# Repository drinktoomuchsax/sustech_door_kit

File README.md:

<div>
<p align="center">

  </p>  
<h1 align="center">
  南科大宿舍门锁套件
</h1>
<p align="center">
  丢掉你的校园卡
</p>
<p align="center">
人脸识别、模糊密码、电子反锁、访客密码、无痕恢复……</a>
</p>
</div>

_This page is not available in [English](README.en.md) yet._ 

:unlock:这个项目使用两片ESP32开发板以及一系列模块，将宿舍开门体验提到了新高度

:star:欢迎Star

:+1:项目采用CC0协议，欢迎复刻、商用、传播

:poop:假如你想在此基础上开发新功能，看不懂屎山代码或有任何疑惑，欢迎issue

---

# :world_map:Table of Contents
- [功能](#功能)
- [原理](#原理)
- [复刻](#复刻)
  - [:money\_with\_wings:物料清单（全功能-预算敏感版本）](#money_with_wings物料清单全功能-预算敏感版本)
  - [:wrench:所需工具](#wrench所需工具)
  - [门的部分](#门的部分)
  - [门内模块（inModule）](#门内模块inmodule)
  - [门外模块（exModule）](#门外模块exmodule)
- [To Do](#to-do)

# 功能

# 原理
拆开门发现有调试的线，详见[博客](wait-to-be-writed)

# 复刻
本项目在开始之初的设计目标之一就是尽可能低的复刻门槛，所以使用的都是现成的市售模块。虽然牺牲了一些集成度和成本，但是你不需要经历繁复地采购和焊接贴片元件，只需少许简单焊接和组装就能复刻本项目。

如果对某一步的详细程度感到不满意或有任何疑惑，欢迎提交issue。

如果你的网络有问题不能加载出图片，可以看南科手册上的版本。

## :money_with_wings:物料清单（全功能-预算敏感版本）
> 第一步，下面全部买回来

| n       | 名称                      | 数量 | 款式                                             | 总价         | 链接                                                                                                                                         | 备注                                                                                                                                                             |
| ------- | ------------------------- | ---- | ------------------------------------------------ | ------------ | -------------------------------------------------------------------------------------------------------------------------------------------- | ---------------------------------------------------------------------------------------------------------------------------------------------------------------- |
| 0       | luat esp32-s3开发板       | 1片  | ESP32S3开发板                                    | ￥29.9        | [淘宝合宙旗舰店](https://item.taobao.com/item.htm?spm=a1z09.2.0.0.67002e8dnQlfYj&id=696836421009&_u=53t2jj8gb611)                            | 可以换其他家，但是记得修改pcb封装尺寸和代码引脚定义                                                                                                              |
| 1       | luat esp32-c3开发板       | 1片  | 经典款ESP32C3开发板                              | ￥12.9        | [淘宝合宙旗舰店](https://item.taobao.com/item.htm?spm=a1z09.2.0.0.67002e8dnQlfYj&id=666579064570&_u=53t2jj8g0ed4)                            | 同上                                                                                                                                                             |
| 2       | 人脸识别模块HLK-FR1002    | 1个  | 【强力推荐】测试套件B: FR1002单模块+端子连接线*1 | ￥72.5        | [淘宝海凌科旗舰店](https://detail.tmall.com/item.htm?_u=53t2jj8g16d6&id=693925937468&skuId=4929017661289&spm=a1z09.2.0.0.67002e8dnQlfYj)     |                                                                                                                                                                  |
| 3       | 雷达模块HLK-LD2420        | 1个  | 【LD2420单模块】24G雷达模块（人体移动微动感应）  | ￥9.9         | [淘宝海凌科旗舰店](https://detail.tmall.com/item.htm?_u=53t2jj8g7db2&id=703242126067&skuId=4954211957536&spm=a1z09.2.0.0.38472e8dTHnsiW)     |                                                                                                                                                                  |
| 4       | 内模块pcb打板             | 1片  | 略                                               | ￥20          | [Gerber文件](pcbDesign/imModule/inModule_Gerber.zip)                                                                                         | 嘉立创价格，可以换其他家，洞洞板手焊（￥2.5），立创eda抄板白嫖（￥0）                                                                                              |
| 5       | 外模块pcb打板             | 1片  | 略                                               | ￥40左右      | [Gerber文件](pcbDesign/exMoudle/sustech_door_kit-exModule-Gerber.zip)                                                                        | 同上，但是需要两片，一片用作焊接，一篇用作背板安装                                                                                                               |
| 6       | 继电器                    | 1个  | 4路5v红板                                        | ￥12          | [淘宝优信电子](https://item.taobao.com/item.htm?spm=a1z09.2.0.0.67002e8dnQlfYj&id=549692985984&_u=53t2jj8gef8e)                              | 要买5v的，不然不能开发板直接触发                                                                                                                                 |
| 6.1     | 16pin排母                 | 6个  | 1*16P单排母座                                    | ￥1           | [淘宝优信电子](https://item.taobao.com/item.htm?spm=a230r.1.14.22.43cb7ce2fQNwRq&id=522579376259&ns=1&abbucket=13#detail)                    | 用来插开发板的。测试供电正常再插上去，不然会烧:(。并且如果每次更新固件都要整个拆下来，麻烦发                                                                     |
| 7       | :keyboard:轴体            | 14个 | cherryMX的封装就能够焊上，具体轴体按需选择       | ￥10          | [淘宝不知名店铺](https://item.taobao.com/item.htm?spm=a1z09.2.0.0.67002e8dnQlfYj&id=626986550029&_u=53t2jj8g20a3)                            |                                                                                                                                                                  |
| 8       | :keyboard:键帽            | 12个 | 标准的十字孔能插上轴体就行                       | ￥6.3         | [桃堡~或者去网吧悄悄扣走windows键~](https://item.taobao.com/item.htm?spm=a21n57.1.0.0.33f6523cuvqG1C&id=704738471960&ns=1&abbucket=0#detail) | 有实力可以加钱上点好的                                                                                                                                           |
| 9       | :nut_and_bolt:M3x25螺丝   | 5个  | 直径3mm，长度25mm，0.5螺距                       | ￥0.3         | [1688](https://detail.1688.com/offer/572533111204.html?spm=a2615.2177701.autotrace-smt_offerGeneral.6.20a22b78zPF4M8)                        | 其实3个就够了，剩下2个惩罚不仔细看备注的强迫症                                                                                                                   |
| 10      | :nut_and_bolt:M3x？？螺丝 | 4个  | 长度？？mm，其余同上                             | ￥5.2         | [1688](https://detail.1688.com/offer/572533111204.html?spm=a2615.2177701.autotrace-smt_offerGeneral.6.20a22b78zPF4M8)                        | 算上邮费                                                                                                                                                         |
| 11      | :nut_and_bolt:M3螺母      | 4个  | 直径M3，六角对边长5.5mm，螺距0.5mm，2.4mm厚      | ￥0.2         | [1688](https://detail.1688.com/offer/572533111204.html?spm=a2615.2177701.autotrace-smt_offerGeneral.6.20a22b78zPF4M8)                        | 邮费算在上面了                                                                                                                                                   |
| 12      | :nut_and_bolt:M3防松螺母  | 3个  | 长度？？mm，其余同上                             | ￥0.2         | [1688](https://detail.1688.com/offer/572533111204.html?spm=a2615.2177701.autotrace-smt_offerGeneral.6.20a22b78zPF4M8)                        | 用来分隔继电器和内模块，邮费算在上面了                                                                                                                           |
| 13      | :electric_plug:硅胶线     | 4条  | 统一1m，18AWG；红色、黑色、黄色、白色            | ￥6           | [桃堡](https://item.taobao.com/item.htm?spm=a1z09.2.0.0.67002e8dnQlfYj&id=654286714565&_u=53t2jj8g48c8)                                      |                                                                                                                                                                  |
| 14      | :electric_plug:CtoC数据线 | 1条  | 1m左右就好                                       | ￥6           | [桃堡](https://detail.tmall.com/item.htm?abbucket=0&id=662435210626&ns=1&spm=a21n57.1.0.0.42b9523caGo622&skuId=4772418768729)                | 如果你经常有连接开发板的需求，推荐合宙的[10条各种版本打包](https://item.taobao.com/item.htm?spm=a1z10.5-c-s.w4002-24045920841.24.230e5aa3n5OKyx&id=706207670841) |
| 15      | DC-DC模块                 | 1个  | 链接里就一个，买他就好                           | ￥5.7         | [桃堡](https://item.taobao.com/item.htm?spm=a1z09.2.0.0.35b32e8dcWQ58H&id=536347025767&_u=53t2jj8g6082)                                      |                                                                                                                                                                  |
| **666** | **总计**                  |      |                                                  | **￥240左右** |

### :moneybag:物料清单（删减功能-预算敏感版本）
如果上述BOM超过了你的预算，可以通过删减功能来减少部件，比如可以删减掉人脸识别功能，避免购买HLK-FR1002和HLK-LD2420将价格减到**153元**。

或者可以eda抄板，节省打板价格。**注意，外模块尺寸为5*13cm，不在立创优惠劵的尺寸范围内，可以试着删减掉人脸识别后将尺寸缩小。**

砍掉一些功能，花上几个小时抄板，修改一下代码，理论最低预算为**86元**。

## :wrench:所需工具
> 如果只是为了复刻项目，下面这些工具不用全部买回来，想办法借到比较合理。但这是个社恐友好的项目，所以放上一些参考购买链接。

| 名称         | 用途       | 参考购买链接                                                                                                                                                                   |
| ------------ | ---------- | ------------------------------------------------------------------------------------------------------------------------------------------------------------------------------ |
| 剥线钳       | 剥线       | [【简装】7寸单色手柄剥线钳](https://detail.tmall.com/item.htm?abbucket=0&id=43540267171&ns=1&spm=a21n57.1.0.0.1f6d523cvhBHgo)                                                  |
| 烙铁         | 焊接       | [标配+C2C数据线+转接板+氮化镓充电器+K65小刀头+BC2尖头 ](https://detail.tmall.com/item.htm?abbucket=0&id=662514528915&ns=1&skuId=4952079646578&spm=a21n57.1.0.0.1f6d523cvhBHgo) |
| 焊锡         | 焊接       | [含锡40%线径0.8mm-50克](https://detail.tmall.com/item.htm?abbucket=0&id=595763429832&ns=1&skuId=4138975609871&spm=a21n57.1.0.0.1f6d523cvhBHgo)                                 |
| 十字螺丝刀   | 打螺丝     | [5*75十字【专业款】](https://item.taobao.com/item.htm?spm=a21n57.1.0.0.33f6523cuvqG1C&id=709830788462&ns=1&abbucket=0#detail)                                                  |
| 扳手         | 打螺母     | [【中小型】活扳手/管钳双功能两用8寸-200mm](https://detail.tmall.com/item.htm?abbucket=0&id=655191633412&ns=1&spm=a21n57.1.0.0.33f6523cuvqG1C&skuId=4992109567932)              |
| 胶布         | 防止短接   | 是个胶布就行                                                                                                                                                                   |
| 美工刀或笔刀 | 剥线       | 最好锋利一点                                                                                                                                                                   |
| 热熔胶枪     | 加固剥线处 | [50W豪华小胶枪+ 10胶棒](https://detail.tmall.com/item.htm?abbucket=0&id=559404680156&ns=1&skuId=4912590361684&spm=a21n57.1.0.0.7fe2523cHBphMQ)                                 |

## 门的部分
### 1.拆门

> 首先，这部分不适合一个人，建议你找一个室友帮忙

> **门只能从内部拆开，平时能够看到2颗裸露的螺丝，大胆地拆。**

> **拆开后把塑料外壳取下，能看到三颗螺丝,前面两颗，后面一颗。拆掉前面两颗整个把手就会掉下来。**

> 这时你应该可以看到内门把手小锁的销被取走了，这就是我们不能从里面反锁的原因。网上没找到合适的，你有时间可以自己建模3D打印一个就能重新获得机械反锁门的能力。

> 因为这部分是后写的，有一些照片因为安装了内模块不能继续拍，sorry

> **内门把手掉下来后，会露出一个框架，有两颗螺丝，这两颗螺丝固定内框架和外门把手**

> 下图是一个，还有一个在更下方

> **一手扶着外门把手，一手拆内框架的螺丝**

> **螺丝拆下来后，内框架会掉下来，外门把手也会掉下来**

> **你应该可以看到掉下来的外门把手框里有一些线连到门里面（忽略图片左方的凝固的热熔胶）**

> **这些线有不同的功能，红线12v供电、黑线地，其他四个颜色短接地会有不同的效果，效果如下表**

| 短接 | 效果                 |
| ---- | -------------------- |
| 黑橙 | 面板变绿，正常开门   |
| 黑绿 | 锁门（面板保持蓝色） |
| 黑黄 | 开门                 |
| 黑白 | 锁门（面板变红）     |

> **你已经看到线了，进入下一步，剥线！**

### 2.剥线

> **这是一个手艺活，比较考验耐心**

> **你需要用美工刀或者笔刀将线的外层剥开，露出里面的金属。注意不要直接切断，特别是红色和黑色的电源线，没人知道这个系统断电重启之后还可能会出现哪些问题**

> **项目只会用到4根线，分别是红色、黑色、黄色、白色。所以你只需要剥4根线**

### 3.焊接延长线

> 这一步可能会比较难

> **线剥好后，剪下你买的[硅胶线](https://item.taobao.com/item.htm?spm=a1z09.2.0.0.67002e8dnQlfYj&id=654286714565&_u=53t2jj8g48c8)，长度需要自己估计一下，大概40cm（估计值，绝对不准）。用[剪线钳](https://detail.tmall.com/item.htm?abbucket=0&id=43540267171&ns=1&spm=a21n57.1.0.0.1f6d523cvhBHgo)剥去两头的线。一端镀锡，一端缠胶布备用**

> **然后给外门把手剥线的地方也镀上锡**

> **然后把对应颜色的线焊上**

> **打上热熔胶防止短接同时加强连接处**

> **最后效果如下（方便研究我把所有都剥了）**

### 4.走线
> **把线首先穿过外门把手上面的小框**

> **然后穿过门上的洞，这样外门把手就不会因为线的存在而不能贴合门体**

> **最后效果如下，平整度没有差别**

### 5.装门

> **然后就是逆向装回去的过程，不多说了**

> **唯一值得注意的点是，可以用一段胶布缠上整束线，然后用一个扎带固定，这样就把拉力转移到扎带部分而不是焊点** 

> **最后效果如下**

> 至此拆门部分结束

## 门内模块（inModule）

### 1.焊接
#### a.开发板排母
#### b.排线
### 2.开发板刷入程序
#### a.更改参数
- bleServerName
- BLE UUIDs
- WiFi name
- WiFi pswd
- realpswd
- 
### 3.安装
#### a.继电器接门内地线
#### b.继电器接开发版控制线、电源线、地线
#### c.测试输出电压
#### d.安装开发板
#### e.热熔胶胶固定
#### f.焊接门内12v电源线

### 4.测试
#### a.WiFi开门功能
#### b.按键功能

## 门外模块（exModule）
### 1.焊接
#### a.电阻、开发板
#### b.雷达、排针
#### c.人脸识别模块

### 2.组装
### 3.开发板刷入程序
#### a.更改参数
### 4.配置模块
#### a.人脸注册
#### b.修改雷达门限
### 5.调试

# To Do
对功能有任何想法和提议，都欢迎提交issue。当然，保证不保证解决。
- [ ] 完善文档
- [ ] 接入homeassistant，让小爱同学开门
- [ ] 通信协议
- [ ] 剩下的两根线
- [ ] 更多的功能
- [ ] 更低的复刻门槛

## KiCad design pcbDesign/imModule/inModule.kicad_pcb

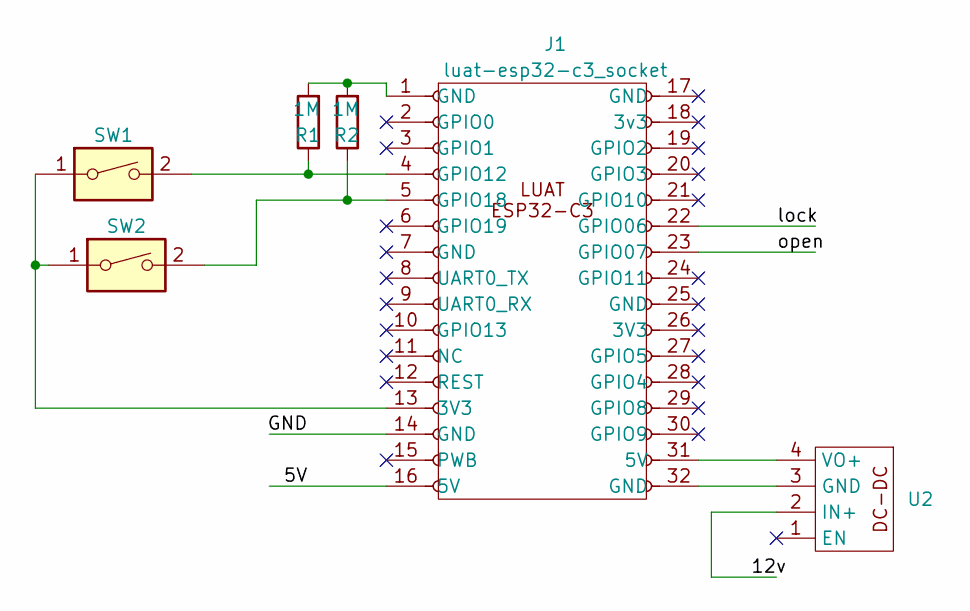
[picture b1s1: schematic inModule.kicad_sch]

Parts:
J1: luat-esp32-c3_socket; luat-esp32-c3-devBoard
R1, R2: 1M; R_Axial_DIN0207_L6.3mm_D2.5mm_P7.62mm_Horizontal
SW1, SW2: SW_DIP_x01; SW_Cherry_MX_1.00u_Plate
U2: taobaoDCDC

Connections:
/5V: J1.16 (5V)
/12v: U2.2 (IN+)
/GND: J1.14 (GND)
/lock: J1.22 (GPIO06)
/open: J1.23 (GPIO07)
unnamed: J1.13 (3V3), SW1.1, SW2.1
unnamed: J1.1 (GND), R1.2, R2.2
unnamed: J1.4 (GPIO12), R1.1, SW1.2
unnamed: J1.5 (GPIO18), R2.1, SW2.2
unnamed: J1.32 (GND), U2.3 (GND)
unnamed: J1.31 (5V), U2.4 (VO+)

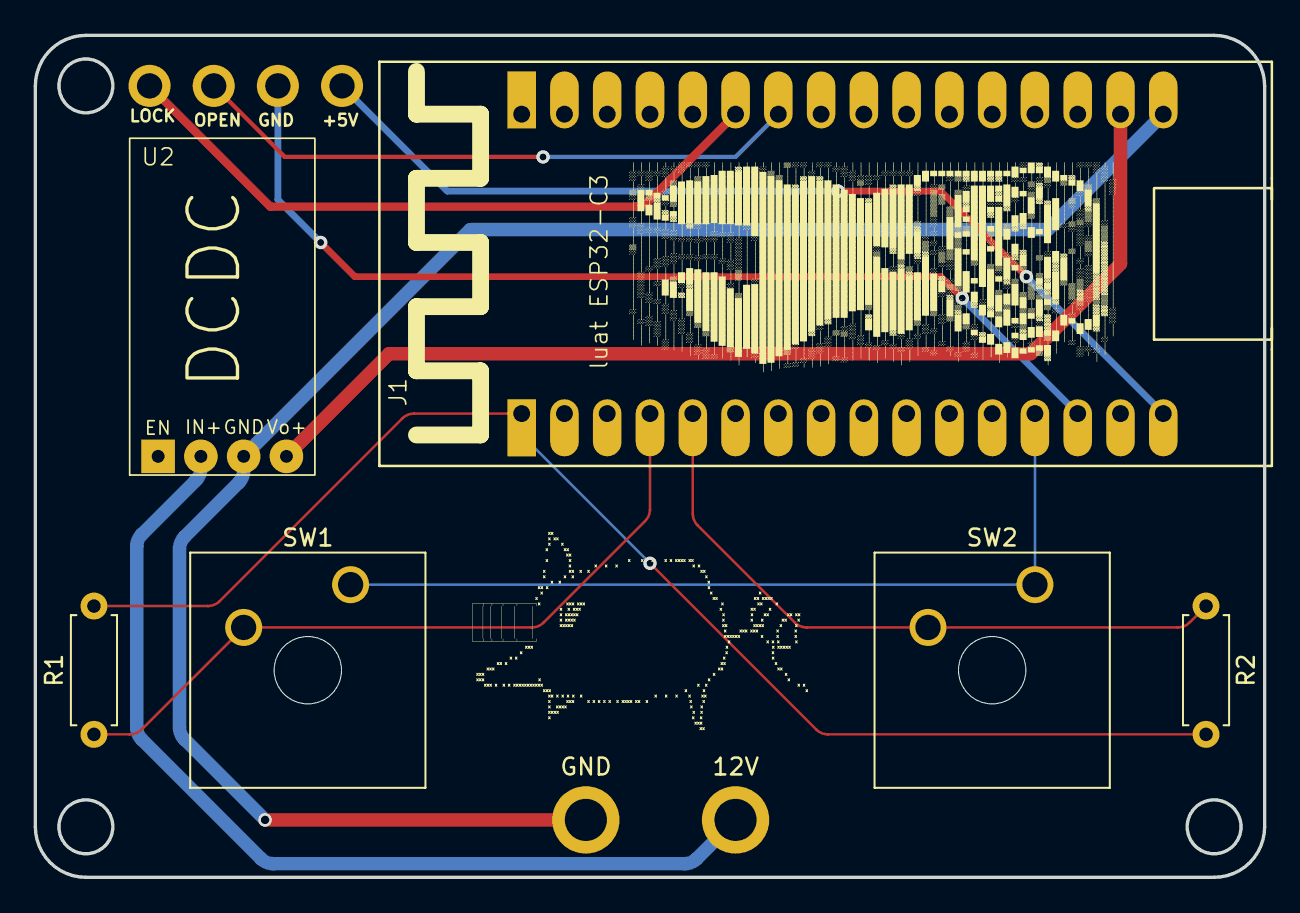
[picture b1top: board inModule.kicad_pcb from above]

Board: 2 copper layers, 73.0 x 50.0 mm, 6 parts (0 on the bottom side), 6 nets.

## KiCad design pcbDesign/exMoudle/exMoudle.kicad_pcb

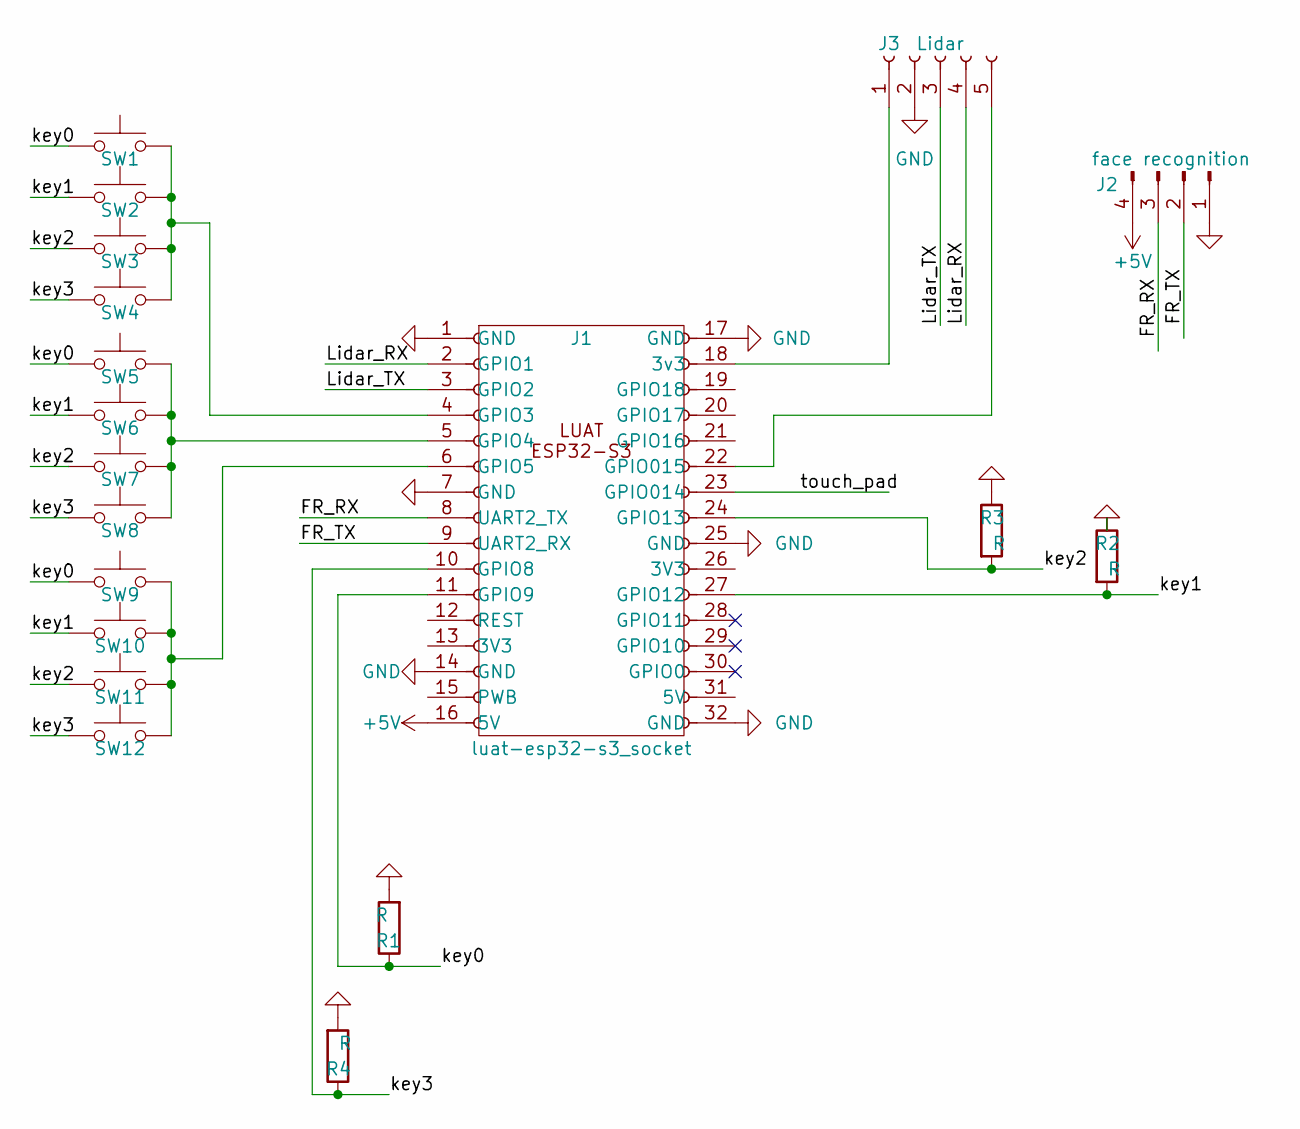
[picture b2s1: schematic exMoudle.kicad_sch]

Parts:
J1: luat-esp32-s3_socket; luat-esp32-s3-devBoard
J2: face recognition; PinHeader_1x04_P2.54mm_Vertical
J3: Lidar; PinSocket_1x05_P2.54mm_Vertical
R1, R2, R3, R4: R; R_Axial_DIN0207_L6.3mm_D2.5mm_P10.16mm_Horizontal
SW1, SW2, SW3, SW4, SW5, SW6, SW7, SW8, SW9, SW10, SW11, SW12: SW_Push; SW_Cherry_MX_1.00u_Plate

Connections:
+5V: J1.16 (5V), J2.4
/FR_RX: J1.8 (UART2_TX), J2.3
/FR_TX: J1.9 (UART2_RX), J2.2
/Lidar_RX: J1.2 (GPIO1), J3.4
/Lidar_TX: J1.3 (GPIO2), J3.3
/key0: J1.11 (GPIO9), R1.1, SW1.1, SW5.1, SW9.1
/key1: J1.27 (GPIO12), R2.2, SW2.1, SW6.1, SW10.1
/key2: J1.24 (GPIO13), R3.2, SW3.1, SW7.1, SW11.1
/key3: J1.10 (GPIO8), R4.1, SW4.1, SW8.1, SW12.1
/touch_pad: J1.23 (GPIO014)
GND: J1.1 (GND), J1.7 (GND), J1.14 (GND), J1.17 (GND), J1.25 (GND), J1.32 (GND), J2.1, J3.2, R1.2, R2.1, R3.1, R4.2
unnamed: J1.18 (3v3), J3.1
unnamed: J1.4 (GPIO3), SW1.2, SW2.2, SW3.2, SW4.2
unnamed: J1.5 (GPIO4), SW5.2, SW6.2, SW7.2, SW8.2
unnamed: J1.6 (GPIO5), SW9.2, SW10.2, SW11.2, SW12.2
unnamed: J1.22 (GPIO015), J3.5

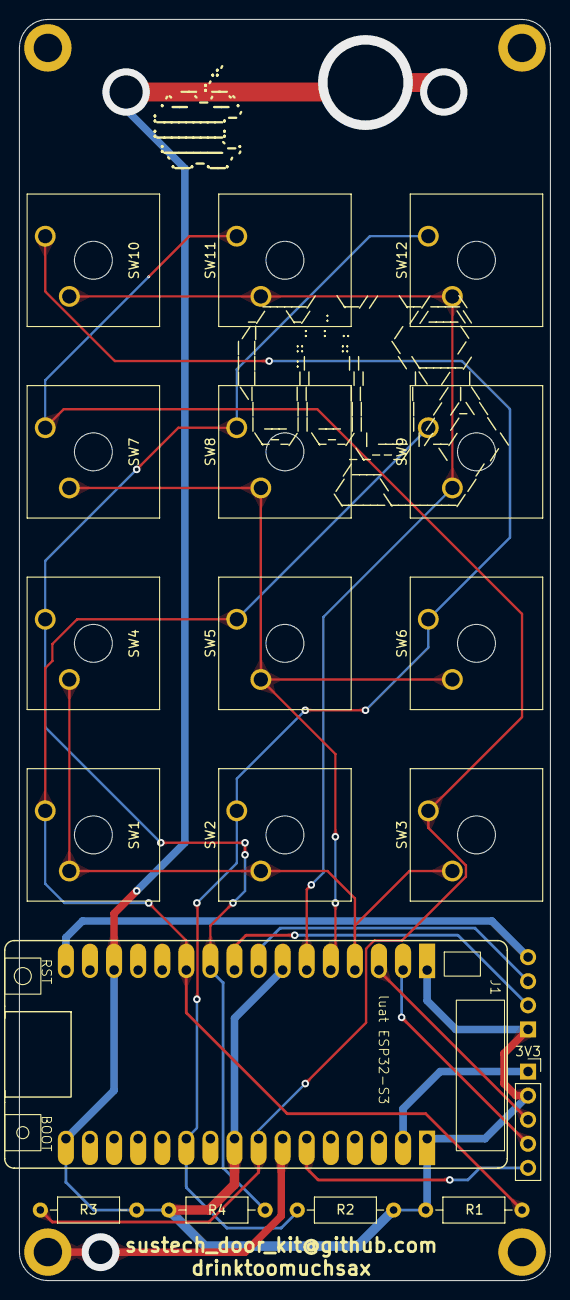
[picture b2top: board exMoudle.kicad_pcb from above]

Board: 2 copper layers, 56.0 x 133.0 mm, 19 parts (1 on the bottom side), 15 nets.

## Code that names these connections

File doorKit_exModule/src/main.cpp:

/**COPYRIGHT DELARE */
/*********
Rui Santos
Complete instructions at https://RandomNerdTutorials.com/esp32-ble-server-client/
Permission is hereby granted, free of charge, to any person obtaining a copy of this software and associated documentation files.
The above copyright notice and this permission notice shall be included in all copies or substantial portions of the Software.
*********/
/*
  Rui Santos
  Complete project details at https://RandomNerdTutorials.com/esp32-client-server-wi-fi/

  Permission is hereby granted, free of charge, to any person obtaining a copy
  of this software and associated documentation files.

  The above copyright notice and this permission notice shall be included in all
  copies or substantial portions of the Software.
*/
/**
 * @author drinktoomuchsax@github.com
 * @date 2023-07-18
 * @copyright The copyright notice and this permission notice shall be included in all copies or substantial portions of the Software.
 */

#include <Arduino.h>
// keyboard part
#include <vector>
using namespace std;
// STATE indicate the state of esp32. It could be syandby, verifyPSWD_wipeJitter, undifened and etc
String STATE = "undifeined";

// BLE part
#include <BLEDevice.h>
#include <BLEServer.h>
#include <BLEUtils.h>
#include <BLE2902.h>
#define bleServerName "1106_door_kit" // BLE server name
bool deviceConnected = false;
#define SERVICE_UUID "91bad492-b950-4226-aa2b-4ede9fa42f59"                                                        // See the following for generating UUIDs: https://www.uuidgenerator.net/
BLECharacteristic openCharacteristics("cba1d466-344c-4be3-ab3f-189f80dd7518", BLECharacteristic::PROPERTY_NOTIFY); // open Characteristic and Descriptor
BLEDescriptor openDescriptor(BLEUUID((uint16_t)0x2902));
BLECharacteristic lockCharacteristics("ca73b3ba-39f6-4ab3-91ae-186dc9577d99", BLECharacteristic::PROPERTY_NOTIFY); // lock Characteristic and Descriptor
BLEDescriptor lockDescriptor(BLEUUID((uint16_t)0x2903));
class MyServerCallbacks : public BLEServerCallbacks // Setup callbacks onConnect and onDisconnect
{
  void onConnect(BLEServer *pServer)
  {
    deviceConnected = true;
  };
  void onDisconnect(BLEServer *pServer)
  {
    deviceConnected = false;
  }
};
/*
 | "o"   | open the door |
 | "l"   | lock the door |
 | "u"   | unlock       |*/
char oPen = 'o';
char lock = 'l';
char unlock = 'u';
bool OPEN = true;
bool LOCK = false;
void sendSignal(char signal, bool openORlock)
{
  if (openORlock)
  {
    char SIGNAL[] = {signal};
    openCharacteristics.setValue(SIGNAL);
    openCharacteristics.notify();
  }
  else if (!openORlock)
  {
    char SIGNAL[] = {signal};
    lockCharacteristics.setValue(SIGNAL);
    lockCharacteristics.notify();
  }
}

// keyboard part
#include <keyboardMatrix.h>
// keyboard part set your password in keyboardMatrix lib
vector<int> pswd;                  // initialize a password vector(array) to store the key user press
vector<int> realpswd;              // realpswd
int keyboardOutput[3] = {3, 4, 5}; // defining gpio output pin
#define key0 9
#define key1 12
#define key2 13
#define key3 8
int keyboardInput[4] = {key0, key1, key2, key3}; // defining gpio input pin
unsigned long lastTime = 0;                      // input timeout
unsigned long timerDelay = 30000;                // 30s

// face recognition part
// face recognition part
// #include <fr1002.h>
HardwareSerial SERfr1002(2); // rename Serial2 into SERfr1002 (stand for serial for fr1002)
uint8_t set_standby[6] = {0xEF, 0xAA, 0x23, 0x00, 0x00, 0x23};
uint8_t get_status[6] = {0xEF, 0xAA, 0x11, 0x00, 0x00, 0x11};
uint8_t go_recognization[8] = {0xEF, 0xAA, 0x12, 0x00, 0x02, 0x00, 0x0A, 0x1A}; // timeout 10s, parity is 0x1A
uint8_t get_usernameANDid[6] = {0xEF, 0xAA, 0x24, 0x00, 0x00, 0x24};

// led setup
const int ledA = 10;
const int ledB = 11;
bool testState = false;
bool lockState = false;

void ledBlink(int whichLed, int circleTime, int gapTime)
{
  if (circleTime > 0)
  {
    for (int Z = 0; Z < circleTime; Z++)
    {
      digitalWrite(whichLed, HIGH);
      delay(gapTime);
      digitalWrite(whichLed, LOW);
      delay(gapTime);
    }
  }
  if (lockState) // long light for lockLED red
    digitalWrite(ledB, HIGH);
  else
    digitalWrite(ledB, LOW);
}

bool switchState(bool state) // switch testState or lockState
{
  if (testState)
  {
    Serial.println("switchState is here");
  }
  if (state)
  {
    if (testState)
      Serial.println("ops false");
    return false;
  }
  else
  {
    if (testState)
      Serial.println("ops true");
    return true;
  }
}

void setup()
{
  Serial.begin(115200);

  // SERfr1002.begin(115200, SERIAL_8N1, 16, 17); // uart port for hlk-fr1002 face recogniton module with baud rate 115200 bps, 8_data_bit, No_parity, 1_stop_bit

  // led setup
  pinMode(ledA, OUTPUT);
  pinMode(ledB, OUTPUT);

  // BLE setup
  BLEDevice::init(bleServerName);                 // Create the BLE Device
  BLEServer *pServer = BLEDevice::createServer(); // Create the BLE Server
  pServer->setCallbacks(new MyServerCallbacks());
  BLEService *doorService = pServer->createService(SERVICE_UUID); // Create the BLE Service
  doorService->addCharacteristic(&openCharacteristics);           // Create BLE Characteristics and Create a BLE Descriptor
  openDescriptor.setValue("open door signal");
  openCharacteristics.addDescriptor(&openDescriptor);
  doorService->addCharacteristic(&lockCharacteristics);
  lockDescriptor.setValue("lock door signal");
  lockCharacteristics.addDescriptor(new BLE2902());
  doorService->start();                                       // Start the service
  BLEAdvertising *pAdvertising = BLEDevice::getAdvertising(); // Start advertising
  pAdvertising->addServiceUUID(SERVICE_UUID);
  pServer->getAdvertising()->start();
  Serial.println("Waiting a client connection to notify...");
}
void loop()
{
  STATE = "standby";

  if (whichKeyPress(keyboardOutput, keyboardInput) != -1)
  {
    lastTime = millis(); // start record time
    STATE = "checkPSWD";
    // keyboard password part, detail look on productdesign.excalidraw
    while ((STATE == "checkPSWD"))
    {
      pswd.push_back(whichKeyPress(keyboardOutput, keyboardInput)); // save the key into an array(actully vector)
      if (pswd.size() == 100)                                       // deal with the jitter
      {
        int keyBeenPressed = wipeJitter(pswd);
        if (keyBeenPressed != -1)
        {
          realpswd.push_back(keyBeenPressed);
          ledBlink(ledA, 1, 50);
          if (testState)
          {
            Serial.printf("add to \"%d\" password\n", keyBeenPressed);
          }
        }
        vector<int> clearpswd; // clear the pswd vector to save memory
        pswd.swap(clearpswd);
      }

      if (whichKeyPress(keyboardOutput, keyboardInput) == -9) // click "#" to enter
      {
        if (testState) // print real pswd
        {
          Serial.print("realpswd is: ");
          for (int i = 0; i < realpswd.size(); i++)
          {
            Serial.printf("_%d", realpswd[i]);
          }
          Serial.println();
        }

        if (verifyPSWD(realpswd) == "TRUE") // match, open the door
        {
          sendSignal(oPen, OPEN);
          ledBlink(ledA, 5, 80);
          STATE = "standby";
          delay(1000);
        }
        else if (verifyPSWD(realpswd) == "LOCK") // match, lock/unlock the door
        {
          lockState = switchState(lockState);
          if (testState)
          {
            if (lockState)
              Serial.print("\nsend lock door signal\n");
            else
              Serial.print("\nsend unlock door signal\n");
          }
          if (lockState)
            sendSignal(lock, LOCK);
          else
            sendSignal(unlock, LOCK);
          STATE = "afterLock";
          delay(1000);
        }
        else if (verifyPSWD(realpswd) == "TEST") // trun on/off test mode
        {
          testState = switchState(testState);
          if (testState)
          {
            Serial.println("test mode");
          }
          else
          {
            Serial.println("exit test mode");
          }
          STATE = "undefined";
        }
        else // do nothing but red led
        {
          Serial.print("verify wrong\n");
          ledBlink(ledB, 5, 80);
          STATE = "undefined";
        };
        realpswd.clear();
      }
      else if (whichKeyPress(keyboardOutput, keyboardInput) == -6) // click "C" to clear
      {
        vector<int> clearpswd;
        pswd.swap(clearpswd);
        realpswd.swap(clearpswd);
        STATE = "clearPSWD";
        delay(500);
      }

      if (((millis() - lastTime) > timerDelay)) // timeout wipe off the pswd and led blink
      {
        vector<int> clearpswd;
        pswd.swap(clearpswd);
        realpswd.swap(clearpswd);
        STATE = "clearPSWD";
        ledBlink(ledB, 5, 200);
        ledBlink(ledA, 5, 200);
      }
    }
  }
  ledBlink(ledB, 0, 0); // refrsh the led for lockLED red
}

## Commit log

2023-06-26 add local file
2023-06-26 add readme
2023-06-26 Update README.md resize headgif
2023-06-26 more documentation
2023-06-26 put door part later in the readme
2023-06-26 增加挟持保护功能
2023-06-27 add fr1002 stm32 example
2023-06-28 add fr1002
2023-06-28 add wifi to inModule!!!
2023-07-03 add pcb design
2023-07-03 switch to cable
2023-07-03 move keyboard coed to saperate library
2023-07-03 som thing wrong with the fxxking git, 30min wasted
2023-07-03 fuck git
2023-07-03 change to cable
2023-07-03 阿萨大大、
2023-07-03 add control buuton on inMoudle
2023-07-03 update inModule button
2023-07-04 change to cheaper esp32-c3
2023-07-05 更新exMoudle pcb，readme增加BOM
2023-07-05 change logo to cable
2023-07-05 readme add tutorial about take apart door
2023-07-05 smaller tutorial jpg
2023-07-05 update readme "take door aprat" tutorial format
2023-07-06 update exModule pcb layout
2023-07-06 updare exModule pcb
2023-07-06 true
2023-07-06 uodate "take door apart" tutorial
2023-07-06 update "take door apart" tutoria;
2023-07-06 update readme intro
2023-07-07 add contribution
2023-07-08 change exModule to esp32-s3
2023-07-09 uodate exModule pcb keyboard
2023-07-09 update inModule pcb add relay holes
2023-07-09 uodate inModule change gpio define
2023-07-09 add serial commnication in inModule
2023-07-09 optimize code in inModule
2023-07-10 add blinking led in exModule
2023-07-10 add test&lockMode in exModule, change Verify
2023-07-10 back up
2023-07-11 i delete the repo then i clone it from github
2023-07-14 figure out cable communication is impossiable
2023-07-15 update ble
2023-07-17 fix inMoudle html open lock state both survive bug
2023-07-17 fix inModule html both open and lock state survive
2023-07-17 update readme bom
2023-07-17 reamde add 南科手册
2023-07-17 readme update install
2023-07-17 for delete workflow
2023-07-18 ble demo
2023-07-18 edit backup
2023-07-18 add copyright
2023-07-18 rename variable in ble. add timeout in exModule
2023-07-18 bug fix for timeout in exModule
2023-07-18 exModule ble immigrante
2023-07-18 intergrate ble into inModule
2023-09-14 Update README.md logo
